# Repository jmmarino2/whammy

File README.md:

# whammy
WHAMMY headphone amplifier, as showed in diyAudio.com

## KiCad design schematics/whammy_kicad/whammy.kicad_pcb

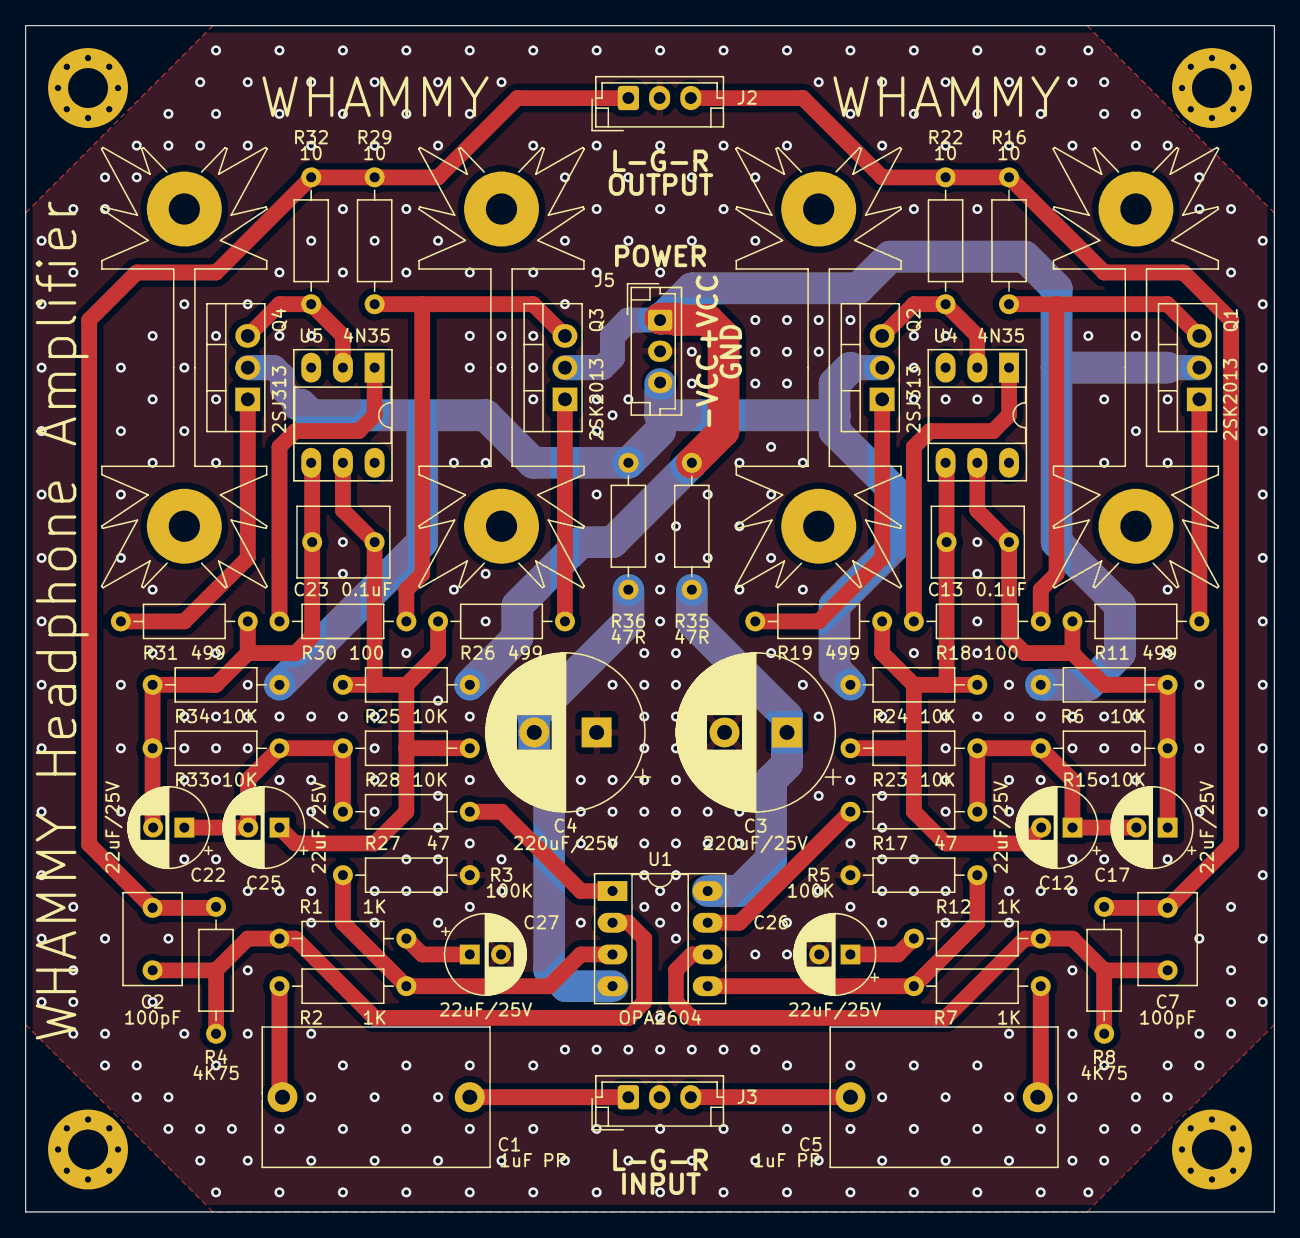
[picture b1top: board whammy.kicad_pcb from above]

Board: 2 copper layers, 100.0 x 95.0 mm, 54 parts (0 on the bottom side), 35 nets.

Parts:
C1, C5: 1uF PP; C_Rect_L18.0mm_W11.0mm_P15.00mm_FKS3_FKP3
C2, C7: 100pF; C_Rect_L7.2mm_W4.5mm_P5.00mm_FKS2_FKP2_MKS2_MKP2
C3, C4: 220uF/25V; CP_Radial_D12.5mm_P5.00mm
C12, C17, C22, C25, C26, C27: 22uF/25V; CP_Radial_D6.3mm_P2.50mm
C13, C23: 0.1uF; C_Rect_L7.2mm_W5.5mm_P5.00mm_FKS2_FKP2_MKS2_MKP2
J2, J3, J5: Conn_01x03; JST_EH_B3B-EH-A_1x03_P2.50mm_Vertical
Q1, Q3: 2SK2013; TO-220-3_Vertical
Q2, Q4: 2SJ313; TO-220-3_Vertical
R1, R2, R7, R12: 1K; R_Axial_DIN0207_L6.3mm_D2.5mm_P10.16mm_Horizontal
R3, R5: 100K; R_Axial_DIN0207_L6.3mm_D2.5mm_P10.16mm_Horizontal
R4, R8: 4K75; R_Axial_DIN0207_L6.3mm_D2.5mm_P10.16mm_Horizontal
R6, R15, R23, R24, R25, R28, R33, R34: 10K; R_Axial_DIN0207_L6.3mm_D2.5mm_P10.16mm_Horizontal
R11, R19, R26, R31: 499; R_Axial_DIN0207_L6.3mm_D2.5mm_P10.16mm_Horizontal
R16, R22, R29, R32: 10; R_Axial_DIN0207_L6.3mm_D2.5mm_P10.16mm_Horizontal
R17, R27: 47; R_Axial_DIN0207_L6.3mm_D2.5mm_P10.16mm_Horizontal
R18, R30: 100; R_Axial_DIN0207_L6.3mm_D2.5mm_P10.16mm_Horizontal
R35, R36: 47R; R_Axial_DIN0207_L6.3mm_D2.5mm_P10.16mm_Horizontal
U1: OPA2604; DIP-8_W7.62mm_Socket_LongPads
U4, U5: 4N35; DIP-6_W7.62mm_Socket_LongPads

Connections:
+15V: J5.1, Q1.2, Q3.2, R6.1, R25.1, R35.1
-15V: J5.3, Q2.2, Q4.2, R24.2, R34.2, R36.2
GND: C3.2, C4.1, C26.2, C27.2, J2.2, J3.2, J5.2, R3.2, R5.2
LEFT_OUT: C7.2, J2.3, R8.2, R16.2, R22.1
unnamed: C1.1, J3.1
unnamed: C1.2, R2.2
unnamed: C2.1, R1.1, R4.1, U1.2
unnamed: C3.1, R35.2, U1.8
unnamed: C4.2, R36.1, U1.4
unnamed: C5.1, J3.3
unnamed: C5.2, R7.2
unnamed: C7.1, R8.1, R12.1, U1.6
unnamed: C12.1, C17.2, R15.2, R17.2, R23.1
unnamed: C12.2, C13.2, R19.1, R23.2, R24.1, U4.4
unnamed: C13.1, C17.1, R6.2, R11.1, R15.1, U4.5
unnamed: C22.1, C25.2, R27.2, R28.2, R33.1
unnamed: C22.2, C23.2, R31.1, R33.2, R34.1, U5.4
unnamed: C23.1, C25.1, R25.2, R26.1, R28.1, U5.5
unnamed: C26.1, R12.2
unnamed: C27.1, R1.2
unnamed: Q1.1, R11.2
unnamed: Q1.3, R16.1, R18.1
unnamed: Q2.1, R19.2
unnamed: Q2.3, R22.2, U4.2
unnamed: Q3.1, R26.2
unnamed: Q3.3, R29.1, R30.1
unnamed: Q4.1, R31.2
unnamed: Q4.3, R32.2, U5.2
unnamed: R2.1, R3.1, U1.3
unnamed: R5.1, R7.1, U1.5
unnamed: R17.1, U1.7
unnamed: R18.2, U4.1
unnamed: R27.1, U1.1
unnamed: R30.2, U5.1
RIGHT_OUT: C2.2, J2.1, R4.2, R29.2, R32.1

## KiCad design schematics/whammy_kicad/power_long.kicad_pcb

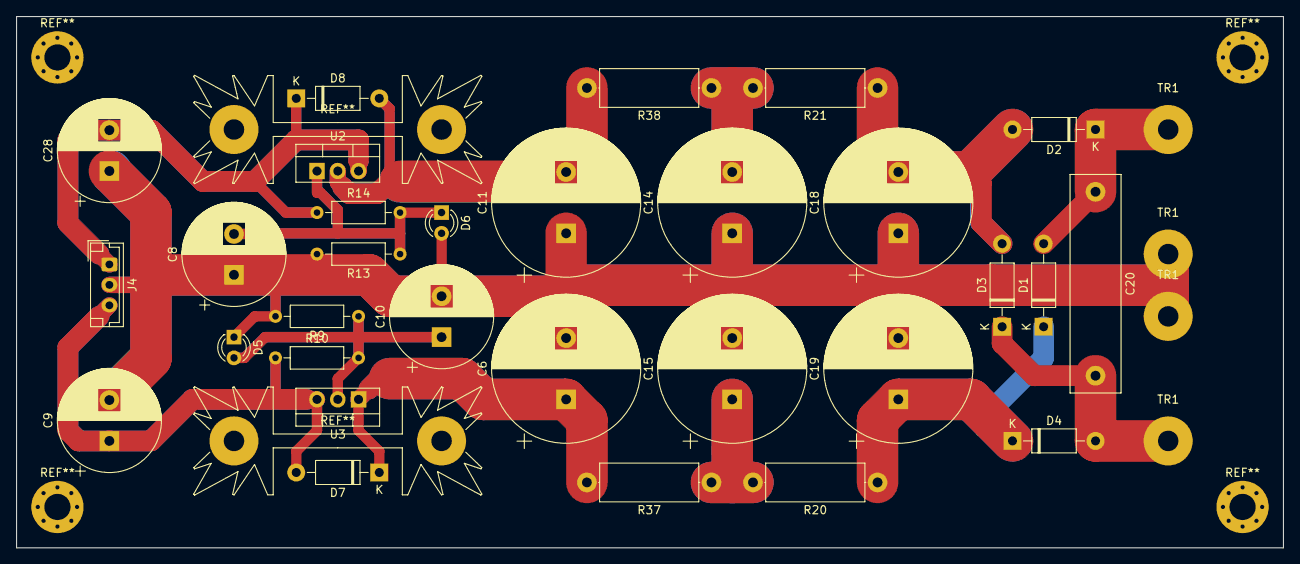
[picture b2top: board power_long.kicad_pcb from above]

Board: 2 copper layers, 155.0 x 65.0 mm, 34 parts (0 on the bottom side), 13 nets.

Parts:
C6, C11, C14, C15, C18, C19: 3300uF/35V; CP_Radial_D18.0mm_P7.50mm
C8, C9, C10, C28: 220uF/50V; CP_Radial_D12.5mm_P5.00mm
C20: .22uF/250V; C_Rect_L26.5mm_W6.0mm_P22.50mm_MKS4
D1, D2, D3, D4, D7, D8: 1N4004; D_DO-41_SOD81_P10.16mm_Horizontal
D5, D6: Red LED; LED_D3.0mm
J4: Conn_01x03; JST_EH_B3B-EH-A_1x03_P2.50mm_Vertical
R9, R13: 330; R_Axial_DIN0207_L6.3mm_D2.5mm_P10.16mm_Horizontal
R10, R14: 1K; R_Axial_DIN0207_L6.3mm_D2.5mm_P10.16mm_Horizontal
R20, R21, R37, R38: 5R1; R_Axial_DIN0414_L11.9mm_D4.5mm_P15.24mm_Horizontal
TR1, TR1#2, TR1#3, TR1#4: SolderWirePad_1x01_Drill2.5mm
U2: L7915; TO-220-3_Vertical
U3: L7815; TO-220-3_Vertical

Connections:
+15V: C9.1, D7.2, J4.3, R10.1, U3.3
-15V: C28.2, D8.1, J4.1, R14.1, U2.3
GND: C6.2, C8.1, C9.2, C10.2, C11.1, C14.1, C15.2, C18.1, C19.2, C28.1, D5.1, D6.2, J4.2, R9.2, R13.2, TR1.5, TR1#2.6
unnamed: C6.1, D7.1, R37.2, U3.1
unnamed: C8.2, D6.1, R13.1, R14.2, U2.1
unnamed: C10.1, D5.2, R9.1, R10.2, U3.2
unnamed: C11.2, D8.2, R38.2, U2.2
unnamed: C14.2, R21.2, R38.1
unnamed: C15.1, R20.2, R37.1
unnamed: C18.2, D2.2, D3.2, R21.1
unnamed: C19.1, D1.1, D4.1, R20.1
unnamed: C20.1, D1.2, D2.1, TR1#4.4
unnamed: C20.2, D3.1, D4.2, TR1#3.7

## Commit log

2021-09-25 First schematics
2021-09-26 Add footprints.
2021-09-26 Add libraries.
2021-09-29 PCB changes
2021-10-09 First PCB version with single heatsinks.
2021-11-10 Final version
